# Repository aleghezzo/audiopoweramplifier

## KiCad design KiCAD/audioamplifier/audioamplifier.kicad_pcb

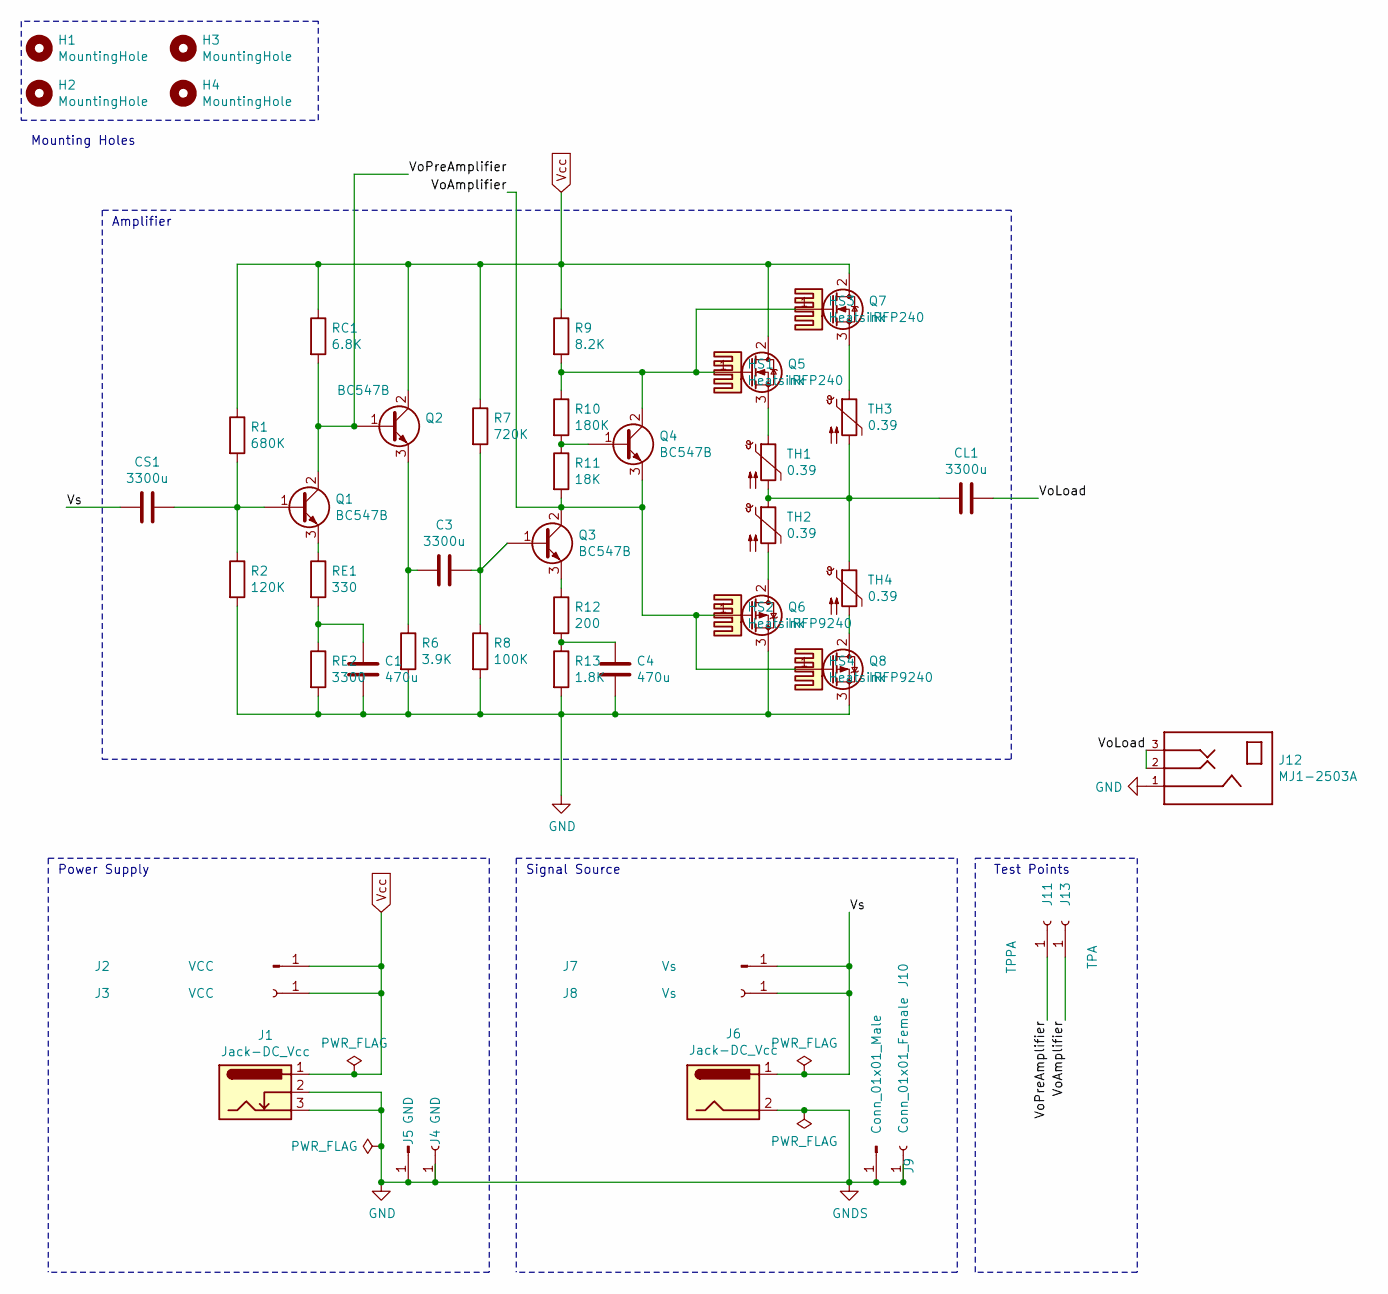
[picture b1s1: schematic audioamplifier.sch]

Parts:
C1, C4: 470u; CP_Radial_D4.0mm_P1.50mm
C3: 3300u; CP_Radial_D4.0mm_P1.50mm
CL1: 3300u; CP_Radial_D4.0mm_P1.50mm
CS1: 3300u; CP_Radial_D4.0mm_P1.50mm
H1, H2, H3, H4: MountingHole; MountingHole_3.2mm_M3
HS1, HS2, HS3, HS4: Heatsink; Heatsink_Stonecold_HS-132_32x14mm_2xFixation1.5mm
J1, J6: Jack-DC_Vcc; BarrelJack_Horizontal
J2, J3: VCC; PinHeader_1x01_P1.00mm_Vertical
J4, J5: GND; PinHeader_1x01_P1.00mm_Vertical
J7, J8: Vs; PinHeader_1x01_P1.00mm_Vertical
J9: Conn_01x01_Male; PinHeader_1x01_P1.00mm_Vertical
J10: Conn_01x01_Female; PinHeader_1x01_P1.00mm_Vertical
J11: TPPA; PinHeader_1x01_P1.00mm_Vertical
J12: MJ1-2503A; CUI_MJ1-2503A; PART_REV A
J13: TPA; PinHeader_1x01_P1.00mm_Vertical
Q1, Q2, Q3, Q4: BC547B; TO-92
Q5, Q7: IRFP240; TO247AC
Q6, Q8: IRFP9240; TO247AC
R1: 680K; R_Axial_DIN0204_L3.6mm_D1.6mm_P5.08mm_Horizontal
R2: 120K; R_Axial_DIN0204_L3.6mm_D1.6mm_P5.08mm_Horizontal
R6: 3.9K; R_Axial_DIN0204_L3.6mm_D1.6mm_P5.08mm_Horizontal
R7: 720K; R_Axial_DIN0204_L3.6mm_D1.6mm_P5.08mm_Horizontal
R8: 100K; R_Axial_DIN0204_L3.6mm_D1.6mm_P5.08mm_Horizontal
R9: 8.2K; R_Axial_DIN0204_L3.6mm_D1.6mm_P5.08mm_Horizontal
R10: 180K; R_Axial_DIN0204_L3.6mm_D1.6mm_P5.08mm_Horizontal
R11: 18K; R_Axial_DIN0204_L3.6mm_D1.6mm_P5.08mm_Horizontal
R12: 200; R_Axial_DIN0204_L3.6mm_D1.6mm_P5.08mm_Horizontal
R13: 1.8K; R_Axial_DIN0204_L3.6mm_D1.6mm_P5.08mm_Horizontal
RC1: 6.8K; R_Axial_DIN0204_L3.6mm_D1.6mm_P5.08mm_Horizontal
RE1: 330; R_Axial_DIN0204_L3.6mm_D1.6mm_P5.08mm_Horizontal
RE2: 3300; R_Axial_DIN0204_L3.6mm_D1.6mm_P5.08mm_Horizontal
TH1, TH2, TH3, TH4: 0.39; R_Axial_DIN0204_L3.6mm_D1.6mm_P5.08mm_Horizontal

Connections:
/VoAmplifier: J13.1, Q3.2 (C), Q4.3 (E), Q6.1 (G), Q8.1 (G), R11.2
/VoLoad: CL1.2, J12.2, J12.3
/VoPreAmplifier: J11.1, Q1.2 (C), Q2.1 (B), RC1.2
/Vs: CS1.1, J6.1, J7.1, J8.1
GND: C1.2, C4.2, J1.2, J1.3, J4.1, J5.1, J6.2, J9.1, J10.1, J12.1, Q6.3 (S), Q8.3 (S), R2.2, R6.2, R8.2, R13.2, RE2.2
unnamed: C1.1, RE1.2, RE2.1
unnamed: C3.1, Q3.1 (B), R7.2, R8.1
unnamed: C3.2, Q2.3 (E), R6.1
unnamed: C4.1, R12.2, R13.1
unnamed: CL1.1, TH1.2, TH2.1, TH3.2, TH4.1
unnamed: CS1.2, Q1.1 (B), R1.2, R2.1
unnamed: Q1.3 (E), RE1.1
unnamed: Q3.3 (E), R12.1
unnamed: Q4.1 (B), R10.2, R11.1
unnamed: Q4.2 (C), Q5.1 (G), Q7.1 (G), R9.2, R10.1
unnamed: Q5.3 (S), TH1.1
unnamed: Q6.2 (D), TH2.2
unnamed: Q7.3 (S), TH3.1
unnamed: Q8.2 (D), TH4.2
Vcc: J1.1, J2.1, J3.1, Q2.2 (C), Q5.2 (D), Q7.2 (D), R1.1, R7.1, R9.1, RC1.1

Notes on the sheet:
Power Supply
Signal Source
Test Points
Mounting Holes
Amplifier

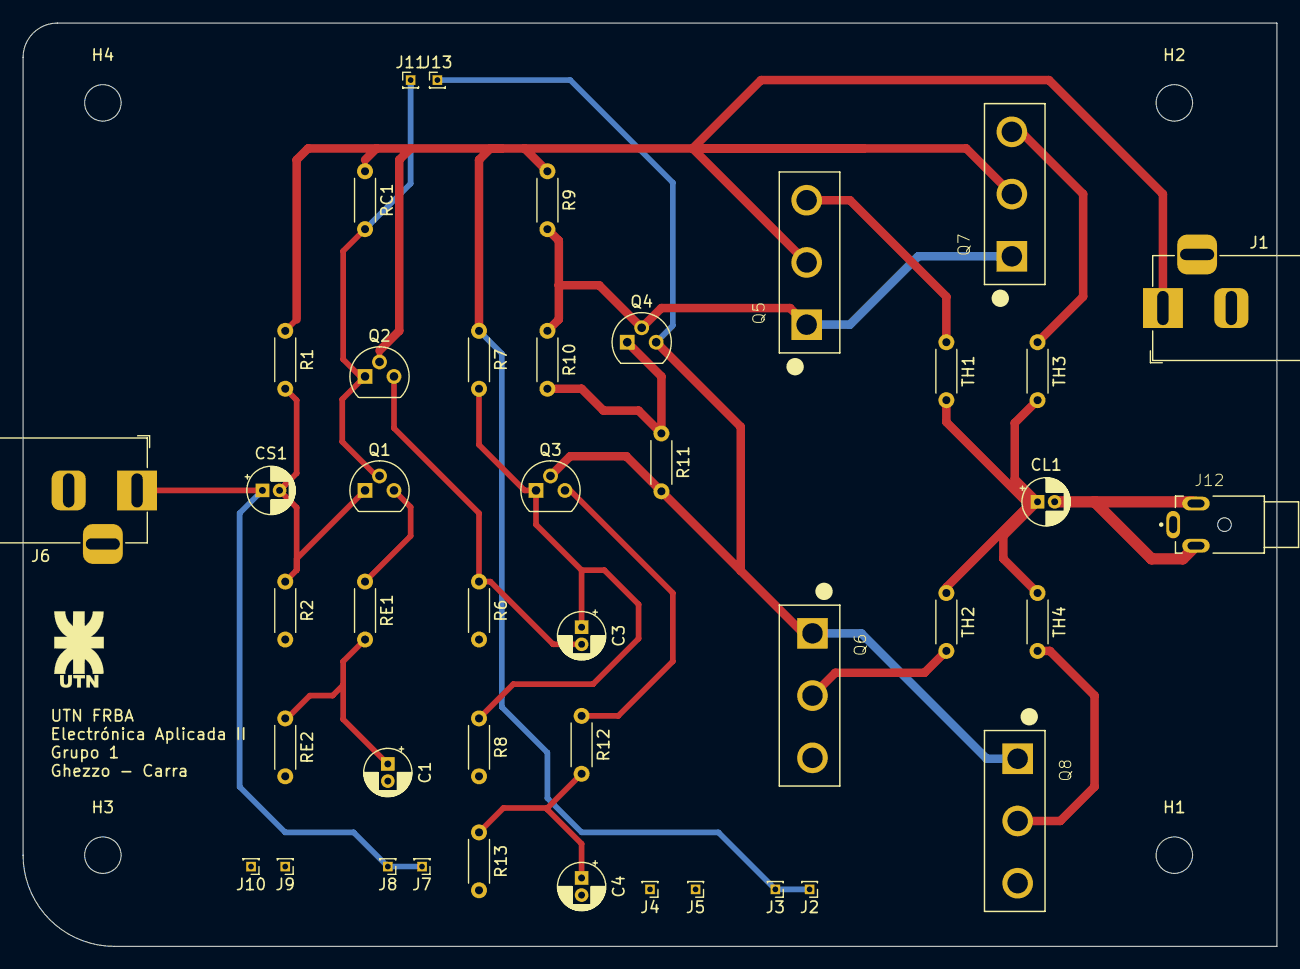
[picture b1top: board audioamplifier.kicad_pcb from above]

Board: 2 copper layers, 110.0 x 81.0 mm, 47 parts (0 on the bottom side), 20 nets.

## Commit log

2021-01-25 Latex
2021-01-25 kicad
2021-01-25 LTSpice
2021-03-01 added final report
